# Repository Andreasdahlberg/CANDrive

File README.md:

# CANDrive
CANDrive is a brushed DC Motor Controller controlled via a [CAN](https://en.wikipedia.org/wiki/CAN_bus) interface.

## Features

* Velocity control
* Torque control
* CAN interface
* Firmware updates over CAN
* Emergency stop
* 5 A output current
* 12-24 V supply voltage

## Getting started

### Getting the Source

This project is [hosted on GitHub](https://github.com/Andreasdahlberg/CANDrive). You can clone this project directly using this command:

```
git clone --recurse-submodules https://github.com/Andreasdahlberg/CANDrive.git
```

### Building

```
scons build-opencm
scons build
```

### Running Tests

Run all tests with valgrind:
```
scons test
```

Run a single test suite:
```
scons app/motor/test && build/motor/test/TestRunner
```

Run a single unit test:
```
scons app/motor/test && build/motor/test/TestRunner test_Motor_SetSpeed
```

### Tools

#### Monitor
The monitor tool is a serial terminal which parses serial output from the device and formats the
output to make it easier to read. It also incorporates a simple command line used for debug commands 
and device configuration. The debug commands are not intended for controlling the motors during normal 
operation since they bypass several of the safety features.

##### Features
* Host timestamps
* Color coded debug levels
* Translation from addresses to file and line
* Command line
* Filtering[Not implemented]

##### Usage
The monitor is started by typing *scons monitor*.
Serial port and baudrate can be configured [here](firmware/config.py) or on the command line, e.g.
*scons monitor SERIAL_PORT=/dev/ttyACM0 BAUD_RATE=921600*

The serial port used by the monitor is available at JP1 and is disabled by default. It can be 
enabled by moving jumper J1.

##### Available commands
###### rpm
rpm \[MOTOR_INDEX\] \[RPM\]

Ex.
```
CANDrive> rpm 0 50
```

###### current
current \[MOTOR_INDEX\] \[CURRENT\]

Ex.
```
CANDrive> current 1 1500
```

###### run
run \[MOTOR_INDEX\]

Ex.
```
CANDrive> run 0
```

###### coast
coast \[MOTOR_INDEX\]

Ex.
```
CANDrive> coast 0
```

###### brake
brake \[MOTOR_INDEX\]

Ex.
```
CANDrive> brake 0
```

###### reset
reset

Ex.
```
CANDrive> reset
```

###### level
level \[MODULE\] \[LEVEL\]

Ex.
```
CANDrive> level App 10
```

###### store
store \[PARAMETER\] \[VALUE\]

Ex.
```
CANDrive> store number_of_motors 1
```

## Hardware
[BOM](https://octopart.com/bom-tool/TDnAzRKf)

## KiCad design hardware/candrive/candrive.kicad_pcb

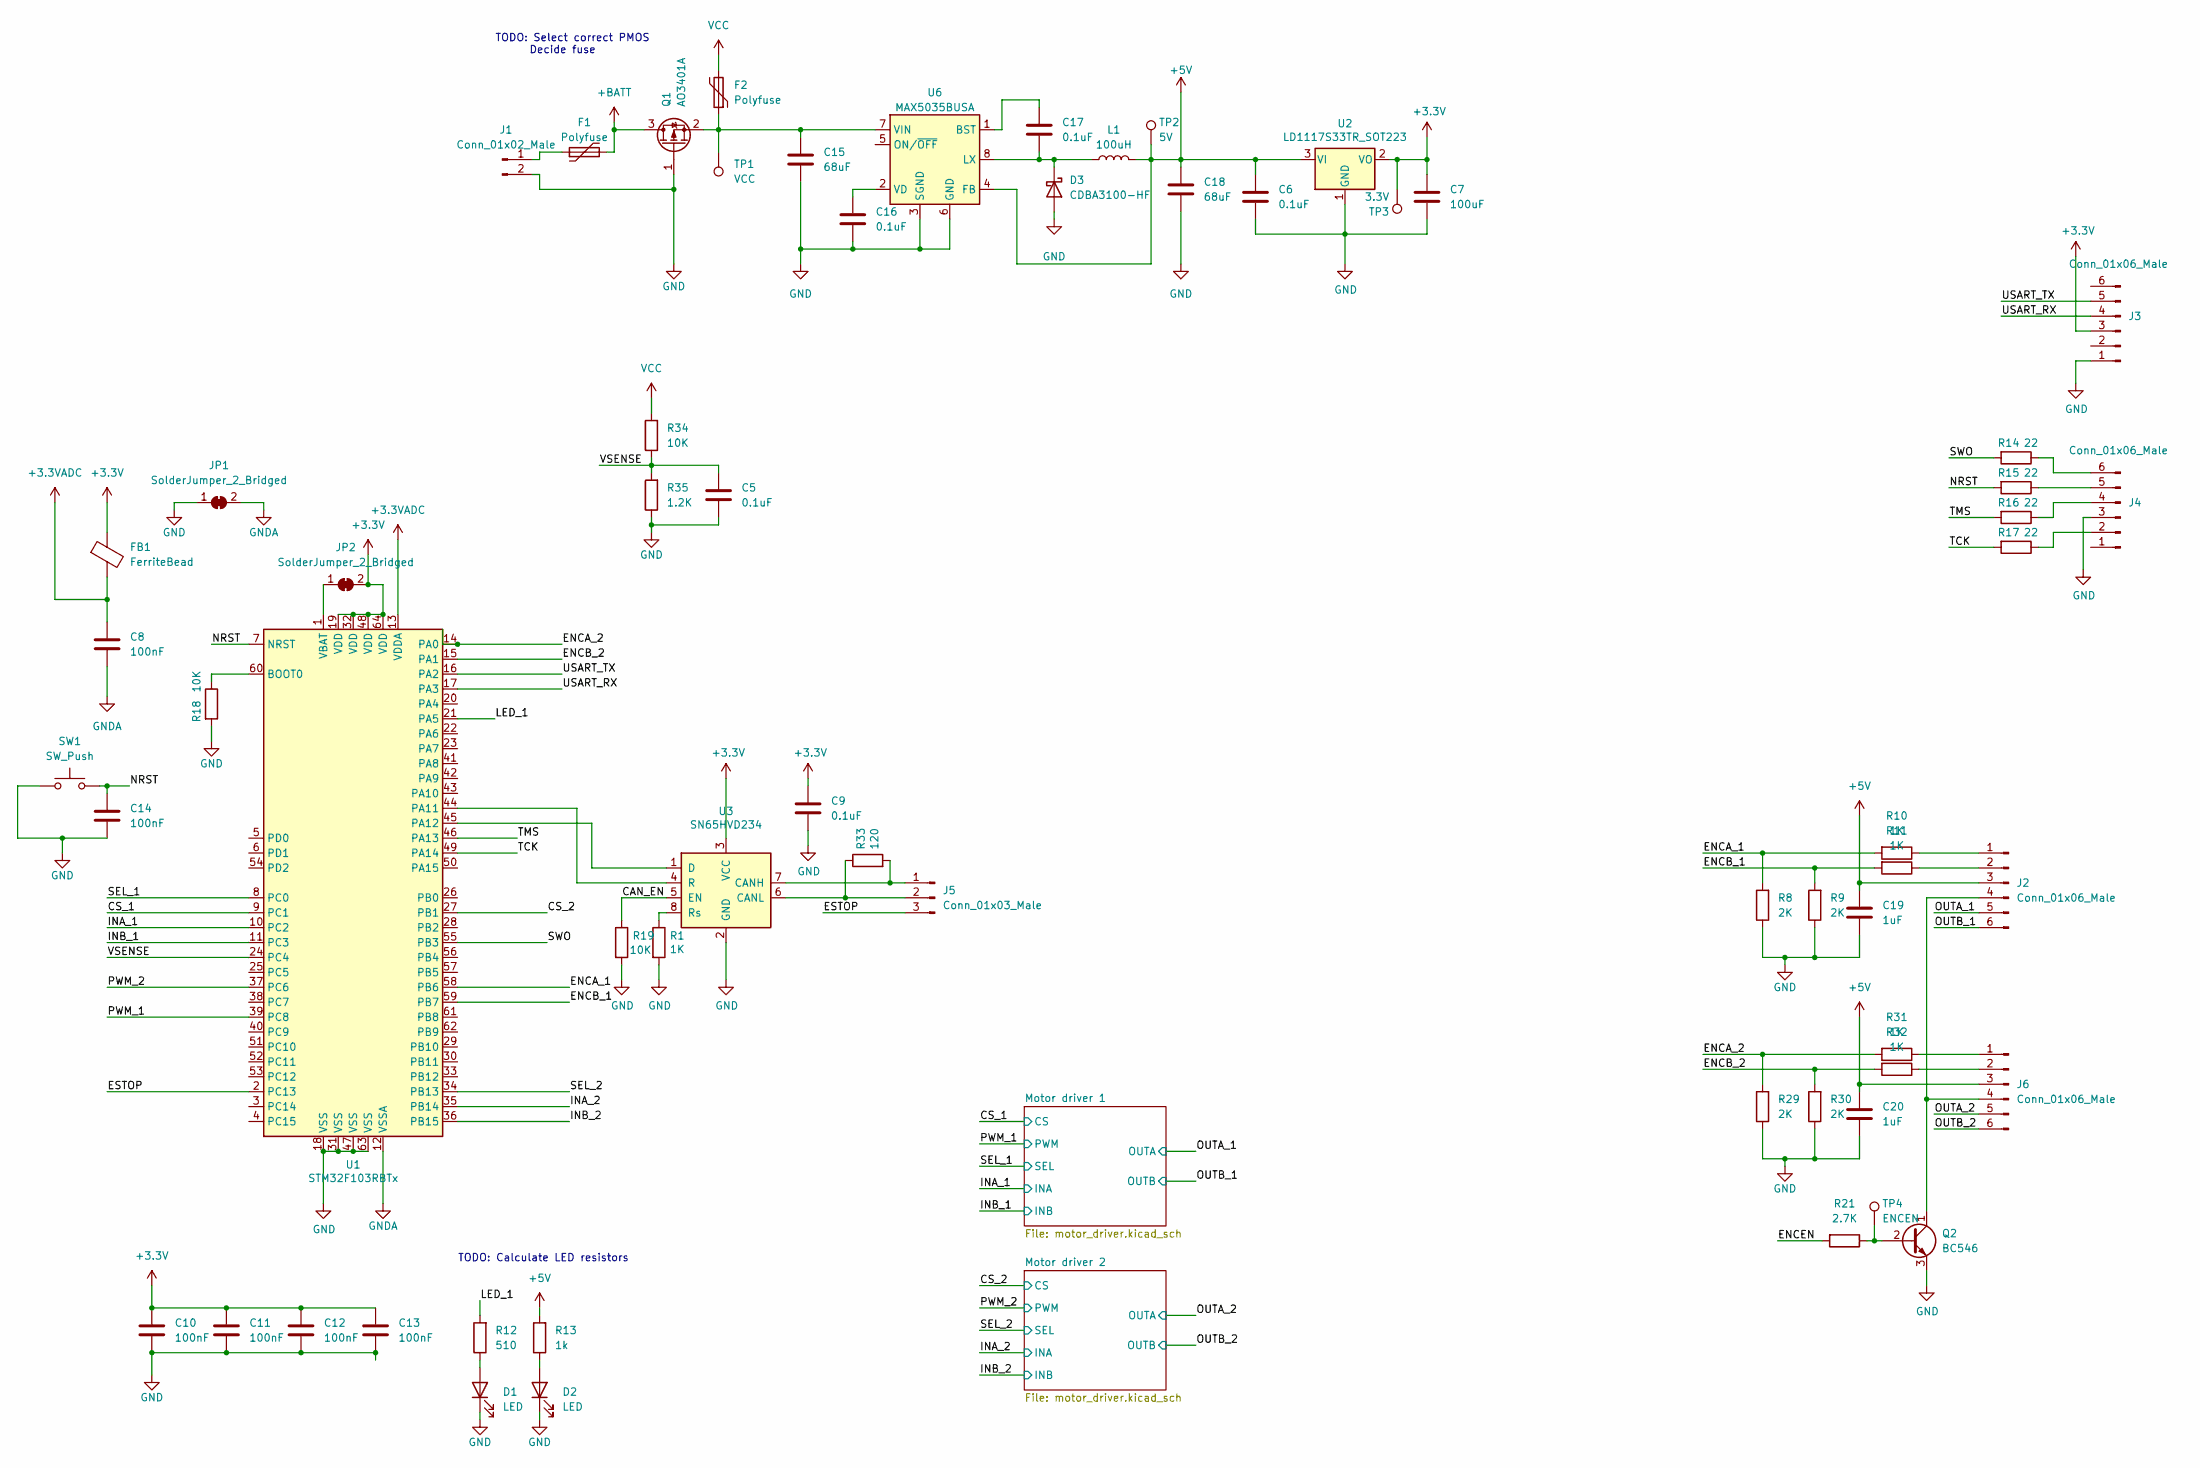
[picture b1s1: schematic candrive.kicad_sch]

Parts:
C5, C6, C9, C16, C17: 0.1uF; C_0805_2012Metric_Pad1.18x1.45mm_HandSolder
C7: 100uF; C_0805_2012Metric_Pad1.18x1.45mm_HandSolder
C8, C10, C11, C12, C13, C14: 100nF; C_0805_2012Metric_Pad1.18x1.45mm_HandSolder
C15, C18: 68uF; C_0805_2012Metric_Pad1.18x1.45mm_HandSolder
C19, C20: 1uF; C_0805_2012Metric_Pad1.18x1.45mm_HandSolder
D1, D2: LED; LED_0805_2012Metric_Pad1.15x1.40mm_HandSolder
D3: CDBA3100-HF; D_SMA
F1, F2: Polyfuse; Fuse_Bourns_MF-RHT300
FB1: FerriteBead; LairdTech_28C0236-0JW-10
J1: Conn_01x02_Male; PinHeader_1x02_P2.54mm_Horizontal
J2, J6: Conn_01x06_Male; PinHeader_1x06_P2.54mm_Horizontal
J3, J4: Conn_01x06_Male; PinHeader_1x06_P2.54mm_Vertical
J5: Conn_01x03_Male; PinHeader_1x03_P2.54mm_Horizontal
JP1, JP2: SolderJumper_2_Bridged; SolderJumper-2_P1.3mm_Open_TrianglePad1.0x1.5mm
L1: 100uH; L_0805_2012Metric_Pad1.05x1.20mm_HandSolder
Q1: AO3401A; SOT-23
Q2: BC546; TO-92_Inline
R1, R10, R11, R31, R32: 1K; R_0805_2012Metric_Pad1.20x1.40mm_HandSolder
R8, R9, R29, R30: 2K; R_0805_2012Metric_Pad1.20x1.40mm_HandSolder
R12: 510; R_0805_2012Metric_Pad1.20x1.40mm_HandSolder
R13: 1k; R_0805_2012Metric_Pad1.20x1.40mm_HandSolder
R14, R15, R16, R17: 22; R_0805_2012Metric_Pad1.20x1.40mm_HandSolder
R18, R19, R34: 10K; R_0805_2012Metric_Pad1.20x1.40mm_HandSolder
R21: 2.7K; R_0805_2012Metric_Pad1.20x1.40mm_HandSolder
R33: 120; R_0805_2012Metric_Pad1.20x1.40mm_HandSolder
R35: 1.2K; R_0805_2012Metric_Pad1.20x1.40mm_HandSolder
SW1: SW_Push; SW_Push_1P1T_NO_CK_KSC6xxJ
TP1: VCC; TestPoint_THTPad_D1.0mm_Drill0.5mm
TP2: 5V; TestPoint_THTPad_D1.0mm_Drill0.5mm
TP3: 3.3V; TestPoint_THTPad_D1.0mm_Drill0.5mm
TP4: ENCEN; TestPoint_THTPad_D1.0mm_Drill0.5mm
U1: STM32F103RBTx; LQFP-64_10x10mm_P0.5mm
U2: LD1117S33TR_SOT223; SOT-223-3_TabPin2
U3: SN65HVD234; SOIC-8_3.9x4.9mm_P1.27mm
U6: MAX5035BUSA; SOIC-8_3.9x4.9mm_P1.27mm

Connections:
+3.3VADC: C8.1, FB1.2, U1.13 (VDDA)
+3V3: C7.1, C9.1, C10.1, C11.1, C12.1, C13.1, FB1.1, J3.3, JP2.2 (B), TP3.1, U1.19 (VDD), U1.32 (VDD), U1.48 (VDD), U1.64 (VDD), U2.2 (VO), U3.3 (VCC)
+5V: C6.1, C18.1, C19.1, C20.1, J2.3, J6.3, L1.2, R13.2, TP2.1, U2.3 (VI), U6.4 (FB)
+BATT: F1.2, Q1.3 (D)
/CAN_EN: R19.1, U3.5 (EN)
/CS_1: U1.9 (PC1); also elsewhere on the board
/CS_2: U1.27 (PB1); also elsewhere on the board
/ENCA_1: R8.2, R10.2, U1.58 (PB6)
/ENCA_2: R29.2, R31.2, U1.14 (PA0)
/ENCB_1: R9.2, R11.2, U1.59 (PB7)
/ENCB_2: R30.2, R32.2, U1.15 (PA1)
/ENCEN: R21.2
/ESTOP: J5.3, U1.2 (PC13)
/INA_1: U1.10 (PC2); also elsewhere on the board
/INA_2: U1.35 (PB14); also elsewhere on the board
/INB_1: U1.11 (PC3); also elsewhere on the board
/INB_2: U1.36 (PB15); also elsewhere on the board
/LED_1: R12.2, U1.21 (PA5)
/NRST: C14.1, R15.2, SW1.2, U1.7 (NRST)
/OUTA_1: J2.5; also elsewhere on the board
/OUTA_2: J6.5; also elsewhere on the board
/OUTB_1: J2.6; also elsewhere on the board
/OUTB_2: J6.6; also elsewhere on the board
/PWM_1: U1.39 (PC8); also elsewhere on the board
/PWM_2: U1.37 (PC6); also elsewhere on the board
/SEL_1: U1.8 (PC0); also elsewhere on the board
/SEL_2: U1.34 (PB13); also elsewhere on the board
/SWO: R14.2, U1.55 (PB3)
/TCK: R17.2, U1.49 (PA14)
/TMS: R16.2, U1.46 (PA13)
/USART_RX: J3.4, U1.17 (PA3)
/USART_TX: J3.5, U1.16 (PA2)
GND: C5.2, C6.2, C7.2, C9.2, C10.2, C11.2, C12.2, C13.2, C14.2, C15.2, C16.2, C18.2, C19.2, C20.2, D1.1 (K), D2.1 (K), D3.2 (A), J1.2, J3.1, J4.3, JP1.1 (A), Q1.1 (G), Q2.3 (E), R1.2, R8.1, R9.1, R18.2, R19.2, R29.1, R30.1, R35.1, SW1.1, U1.18 (VSS), U1.31 (VSS), U1.47 (VSS), U1.63 (VSS), U2.1 (GND), U3.2 (GND), U6.3 (SGND), U6.6 (GND); also elsewhere on the board
GNDA: C8.2, JP1.2 (B), U1.12 (VSSA)
unnamed: C5.1, R34.1, R35.2, U1.24 (PC4)
unnamed: C15.1, F2.1, Q1.2 (S), TP1.1, U6.7 (VIN)
unnamed: C16.1, U6.2 (VD)
unnamed: C17.1, U6.1 (BST)
unnamed: C17.2, D3.1 (K), L1.1, U6.8 (LX)
unnamed: D1.2 (A), R12.1
unnamed: D2.2 (A), R13.1
unnamed: F1.1, J1.1
unnamed: J2.1, R10.1
unnamed: J2.2, R11.1
unnamed: J2.4, J6.4, Q2.1 (C)
unnamed: J4.2, R17.1
unnamed: J4.4, R16.1
unnamed: J4.5, R15.1
unnamed: J4.6, R14.1
unnamed: J5.1, R33.2, U3.7 (CANH)
unnamed: J5.2, R33.1, U3.6 (CANL)
unnamed: J6.1, R31.1
unnamed: J6.2, R32.1
unnamed: JP2.1 (A), U1.1 (VBAT)
unnamed: Q2.2 (B), R21.1, TP4.1
unnamed: R1.1, U3.8 (Rs)
unnamed: R18.1, U1.60 (BOOT0)
unnamed: U1.44 (PA11), U3.4 (R)
unnamed: U1.45 (PA12), U3.1 (D)
VCC: F2.2, R34.2; also elsewhere on the board

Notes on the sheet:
TODO: Calculate LED resistors
TODO: Select correct PMOS Decide fuse

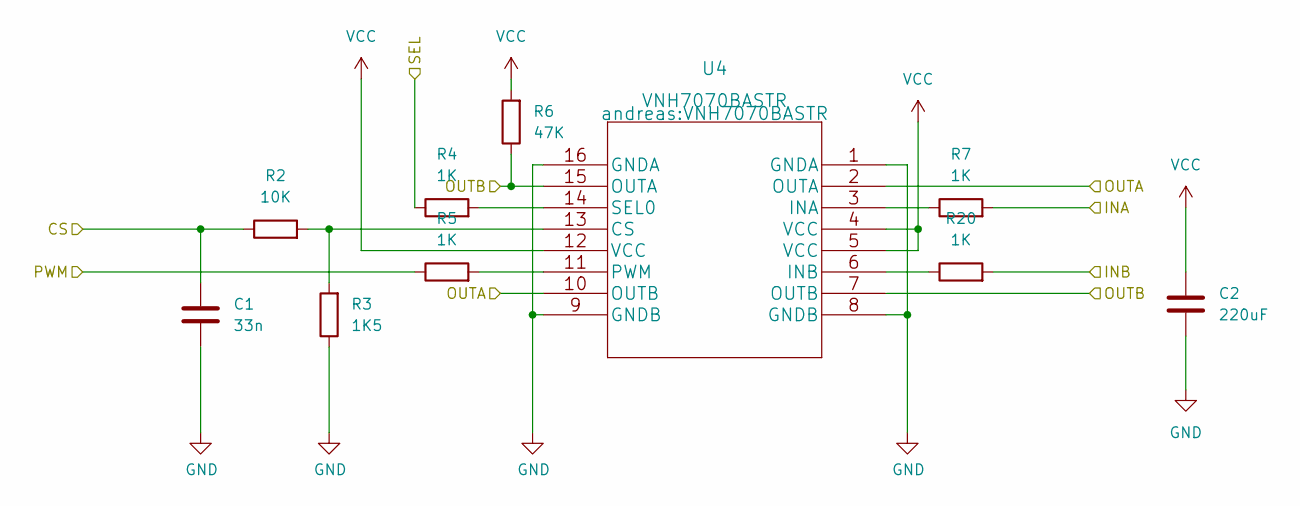
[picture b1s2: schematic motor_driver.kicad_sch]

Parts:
C1: 33n; C_0805_2012Metric_Pad1.18x1.45mm_HandSolder
C2: 220uF; C_0805_2012Metric_Pad1.18x1.45mm_HandSolder
R2: 10K; R_0805_2012Metric_Pad1.20x1.40mm_HandSolder
R3: 1K5; R_0805_2012Metric_Pad1.20x1.40mm_HandSolder
R4, R5, R7, R20: 1K; R_0805_2012Metric_Pad1.20x1.40mm_HandSolder
R6: 47K; R_0805_2012Metric_Pad1.20x1.40mm_HandSolder
U4: VNH7070BASTR

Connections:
/CS_1: C1.1, R2.1; also elsewhere on the board
/INA_1: R7.2; also elsewhere on the board
/INB_1: R20.2; also elsewhere on the board
/OUTA_1: U4.2 (OUTA), U4.10 (OUTB); also elsewhere on the board
/OUTB_1: R6.1, U4.7 (OUTB), U4.15 (OUTA); also elsewhere on the board
/PWM_1: R5.1; also elsewhere on the board
/SEL_1: R4.1; also elsewhere on the board
GND: C1.2, C2.2, R3.1, U4.1 (GNDA), U4.8 (GNDB), U4.9 (GNDB), U4.16 (GNDA); also elsewhere on the board
unnamed: R2.2, R3.2, U4.13 (CS)
unnamed: R4.2, U4.14 (SEL0)
unnamed: R5.2, U4.11 (PWM)
unnamed: R7.1, U4.3 (INA)
unnamed: R20.1, U4.6 (INB)
VCC: C2.1, R6.2, U4.4 (VCC), U4.5 (VCC), U4.12 (VCC); also elsewhere on the board

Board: 4 copper layers, 80 parts (0 on the bottom side), 68 nets, no tracks yet.

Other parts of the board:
C3: 33n; C_0805_2012Metric_Pad1.18x1.45mm_HandSolder
C4: 220uF; C_0805_2012Metric_Pad1.18x1.45mm_HandSolder
R22: 10K; R_0805_2012Metric_Pad1.20x1.40mm_HandSolder
R23: 1K5; R_0805_2012Metric_Pad1.20x1.40mm_HandSolder
R24, R25, R27, R28: 1K; R_0805_2012Metric_Pad1.20x1.40mm_HandSolder
R26: 47K; R_0805_2012Metric_Pad1.20x1.40mm_HandSolder
U5: VNH7070BASTR

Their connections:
/CS_2: C3.1, R22.1; also elsewhere on the board
/INA_2: R27.2; also elsewhere on the board
/INB_2: R28.2; also elsewhere on the board
/OUTA_2: U5.2 (OUTA), U5.10 (OUTB); also elsewhere on the board
/OUTB_2: R26.1, U5.7 (OUTB), U5.15 (OUTA); also elsewhere on the board
/PWM_2: R25.1; also elsewhere on the board
/SEL_2: R24.1; also elsewhere on the board
GND: C3.2, C4.2, R23.1, U5.1 (GNDA), U5.8 (GNDB), U5.9 (GNDB), U5.16 (GNDA); also elsewhere on the board
unnamed: R22.2, R23.2, U5.13 (CS)
unnamed: R24.2, U5.14 (SEL0)
unnamed: R25.2, U5.11 (PWM)
unnamed: R27.1, U5.3 (INA)
unnamed: R28.1, U5.6 (INB)
VCC: C4.1, R26.2, U5.4 (VCC), U5.5 (VCC), U5.12 (VCC); also elsewhere on the board

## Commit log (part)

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2021-12-23 Update config mock
2021-12-23 Use PID parameters from config
2021-12-23 Add PID parameters to config dump
2021-12-23 Set debug level to INFO in signal handler
2021-12-23 Fix code smell
2021-12-23 Fix implicit type conversions
2021-12-23 Fix sonar bug
2021-12-23 Refactor config module
2021-12-23 Add PID parameters to config
2021-12-26 Add values to dbc
2021-12-26 Implement command line in monitor script
2021-12-28 Add imin parameter to config
2021-12-28 Add more parameters to config dump
2021-12-28 Change default debug level to INFO in application
2021-12-29 Add missing test to PID test runner
2021-12-29 Add imin and cvmin parameters in PID controller
2021-12-29 Set imin and cvmin in motor controller
2021-12-29 Fix compiler warning
2021-12-29 Implement support for running motor in reverse
2021-12-29 Improve test coverage in motor module
2021-12-29 Add mode signal
2021-12-29 Only brake/coast if not braking/coasting
2021-12-29 Implement mode signal handlers
2021-12-29 Adjust default log levels
2021-12-29 Update board info logging format
2022-01-01 Implement prototype python interface for candrive
2022-01-01 Update monitor image in README
2022-01-01 Print git version at start
2022-01-01 Update include paths for signal handler
2022-01-01 Remove unused import
2022-01-03 Fix issue with rpm spikes at low speeds
2022-01-05 Fix issue with incorrect rpm at fast motor acceleration
    Caused by voltage drop and noise on the encoder signals. Fixed
    by enabling input capture filtering. This might need some tweaking
    later on when running on the real hardware.
2022-01-05 Fix issue with mode changes ignoring emergency stop
2022-01-05 Improve precision when scaling cv in PID controller
2022-01-05 Eliminate derivative kick in PID controller
2022-01-05 Increase motor pid/speed update frequency
2022-01-05 Fix missing output after entering command in monitor
2022-01-05 Add support for running commands from file
2022-01-05 Fix issue with changing polarity when decreasing speed
2022-01-05 Increase resolution of speed and duty cycle
2022-01-07 Add optional argument to can listener callback
2022-01-11 Fix #22
2022-01-11 Implement byte stream module
2022-01-11 Implement 'GetAvailableSlots' in FIFO module
2022-01-11 Increas max number of listeners to CAN interface
2022-01-11 Increase max number of loggers
2022-01-14 Fix Github actions install failure
2022-01-15 Implement ISO15765-2/ISOTP module
2022-01-15 Fix issue with full frame buffer in signal handler
    Caused by ISO-TP frames pushed to the signal handler frame buffer.
2022-01-15 Increase max number of listeners to the CAN interface
2022-01-15 Fix valgrind error
2022-01-15 Set correct default log level in ISO-TP module
2022-01-15 Improve logging in ISO-TP module
2022-01-15 Remove unused function prototype
2022-01-17 Implement microsecond timer
2022-01-17 Fix issue with incorrect ISO-TP frame order
2022-01-17 Fix incorrect microsecond calculation
2022-01-17 Add support for separation time in ISO-TP module
2022-01-17 Fix implicit cast
2022-01-17 Implement ISO-TP test script
2022-01-17 Improve ISO-TP separation time unit test
2022-01-18 Update mocks
2022-01-18 Rearange includes in the board module
2022-01-18 Add unit tests for the board module
2022-01-18 Decrease ADC calibration delay
2022-01-19 Clean up include paths
2022-01-19 Fix issue with incorrect test coverage information
2022-01-19 Fix issue with incorrect length on truncated string
2022-01-19 Add unit tests for the utility module
2022-01-23 Implement basic bootloader
2022-01-23 Add bootloader build job to CI
2022-01-23 Temporary fix for cantools error
2022-01-24 Replace assert that could fail during normal operation
2022-01-25 Revert "Temporary fix for cantools error"
    This reverts commit 2ff5046d939c9bc0a432122c0790aa7665188542.
2022-01-25 Read NVS location and size from linker script
2022-01-26 Implement function to get the backup register address
2022-01-26 Add pwr mock
2022-01-26 Fix broken restart loop detection
    Use backup registers instead of RAM to store restart information.
2022-01-26 Add RX- and TX-ID parameters to config
2022-01-26 Add monitor script to configure a device
2022-01-28 Fix issue with incorrect RPM during high CPU load
2022-01-28 Implement function to get the firmware upgrade partition address
2022-01-28 Update device configuration script
2022-01-28 Add mock functions for the ISO-TP module
2022-01-28 Add documentation to the ISO-TP module
2022-01-28 Add bin-file builder
2022-01-28 Fix typo
2022-01-31 Implement basic application selection in bootloader
2022-01-31 Increase number of loggers
2022-02-04 Implement firmware manager
2022-02-07 Implement flash helper module
2022-02-07 Use new flash helper module
2022-02-08 Add more unit tests
2022-02-08 Refactor firmware manager
2022-02-08 Set correct debug level in flash module
2022-02-09 Fix tx conflict in firmware manager
2022-02-09 Add more unit tests for firmware manager
2022-02-09 Refactor firmware manager unit tests
2022-02-13 Fix issue with failed CAN transmit
    This might need some more work, maybe use a tx fifo and interrupts
    instead of a blocking wait.
2022-02-15 Add stream for TX data in isotp module
2022-02-17 Improve unit tests for the ISOTP module
2022-02-18 Configure sonarcloud test execution settings
2022-02-20 Convert test reports to Generic Test Execution format
2022-03-14 Remove support for two different app slots
2022-03-27 Move libopencm3 to src
2022-03-27 Ignore vscode files
2022-03-27 Restructure firmware source
2022-03-29 [WIP] Add deploy step
2022-03-29 Add deploy step in Github Actions
    Add step to deploy both symbol- and firmware-files to Memfault.
2022-04-01 Add missing application unit tests
2022-04-01 Fix incorrect include path
2022-04-01 Add software version
2022-04-07 Remove commented code
2022-04-07 Use custom linker script for the application
2022-04-07 Fix missing and unused includes
2022-04-07 Refactor bootloader and firmware header
2022-04-08 Fix broken test
2022-04-08 Ignore bin files
2022-04-08 Flash bin file instead of hex
2022-04-08 Add CRC and size to bin file
2022-04-20 Add build ID to application
2022-04-20 Print build ID at start
2022-04-20 Removed orig file
2022-04-20 Add unit test skeleton for image module
2022-04-25 Implement image CRC check
2022-04-25 Fix potential buffer overflow issue
2022-04-25 Add missing init of Image module in unit tests
2022-04-26 Implement function to get image type as string
2022-04-28 Print image type in bootloader
2022-04-28 Increase allowed max size of bootloader
2022-04-28 Update board mock
2022-05-06 Fix incorrect vector table alignment
2022-06-03 Move motor config to board module
2022-06-09 Implement NVCom module
    This module handles communication between bootloader and application.
2022-06-09 Adapt firmware manager for use in bootloader
2022-06-09 Update image module mock
2022-06-09 Increase max number of console commands
2022-06-09 Implement update console command
2022-06-12 Fix broken motor controller test suite
2022-06-12 Use NVCom in system monitor
2022-06-12 Fix code format
2022-06-12 Fetch reset flags from system monitor
2022-06-13 Fix code smells
2022-06-13 Improve test coverage in firmware manager
2022-06-14 Implement firmware update in bootloader
2022-06-14 Move application commands to a separate file
2022-06-16 Adapt firmware update script to new bootloader
2022-06-16 Set correct log level in image module
2022-06-17 Implement function to check if a firmware download is ongoing
2022-06-17 Implement status LED in the bootloader
2022-07-18 Fix ovelapping buffers
2022-07-21 Add update message type
2022-07-21 Add action checks in firmware manager
    Add support for injection callbacks to action checks used to
    determine if an action, e.g. reset, is allowed.
    Also use callback for reset instead of direct call.
2022-07-21 Integrate new firmware manager functionality
2022-07-21 Update firmware update script with new message type
2022-07-22 Add more tests for reset request
2022-07-22 Add tests for the update request
2022-07-22 Add test for reset/update allowed check
2022-07-29 Fix incorrect bit mask in ADC driver
2022-08-05 Start ADC conversions at start up
2022-08-05 Add filter to motor current readings
2022-08-05 Add filter mock
2022-08-07 Fix broken current control
2022-08-07 Change signal names
    Also restructures and clean up in the DBC file.
2022-08-10 Add ISOTP signals to DBC file
2022-08-10 Update signal names in python interface
2022-08-10 Add python shebang to firmware update script
2022-10-25 Move CAN-pins to PortA
2022-10-25 Fix incorrect usage of GPIO remap function
2022-10-25 Improve logging when using two motors
2022-10-25 Use const variables for input capture channel config
2022-10-25 Add configuration for second motor
2022-10-25 Fix incorrect paths in test report
2022-11-08 Update gitignore
2022-11-08 Update device schematic
2022-11-08 Add noinit section
2022-11-11 Remove unused module
2022-11-11 Exclude third party code from sonarscan
2022-11-11 Add memfault support with basic configuration
2022-11-11 Implement a device monitoring wrapper
2022-11-11 Add missing submodule
2022-11-11 Add missing mock return value
2022-11-11 Update device monitoring mock
2022-11-11 Enable device monitoring
2022-11-11 Fix ISO-TP failure after FC timeout
    The buffer was not cleared after a FC timeout so several failed
    messages could fill up the stream buffer with no way to recover.
2022-11-11 Add transport mock
2022-11-12 Add missing include
2022-11-13 Update application unit tests
2022-11-13 Add Memfault mock functions
2022-11-13 Add unit tests device monitoring
2022-11-14 Handle ISOTP errors in device monitoring transport layer
2022-11-14 Update outdated function documentation
2022-11-16 Add unit test for reset command
2022-11-16 Add unit test for dump data command
2022-11-17 Implement IsSending-function in ISOTP module
2022-11-17 Improve error handling in device monitoring transport layer
2022-11-17 Improve test coverage
2022-11-17 Fix failed Github actions build
    Lock ubuntu version to 20.04.
2022-11-28 Fix broken DMA mock
2022-11-28 Increase max number of ADC channels
2022-11-28 Handle system monitor fail state in application
2022-11-28 Move ADC init before system monitor init
2022-11-28 Implement VSense to voltage function
2024-01-24 Fix broken format command
2024-01-24 Implement basic vsense monitoring

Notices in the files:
parts and their libraries:
Copyright 2021 Accelerated Designs. All rights reserved.
